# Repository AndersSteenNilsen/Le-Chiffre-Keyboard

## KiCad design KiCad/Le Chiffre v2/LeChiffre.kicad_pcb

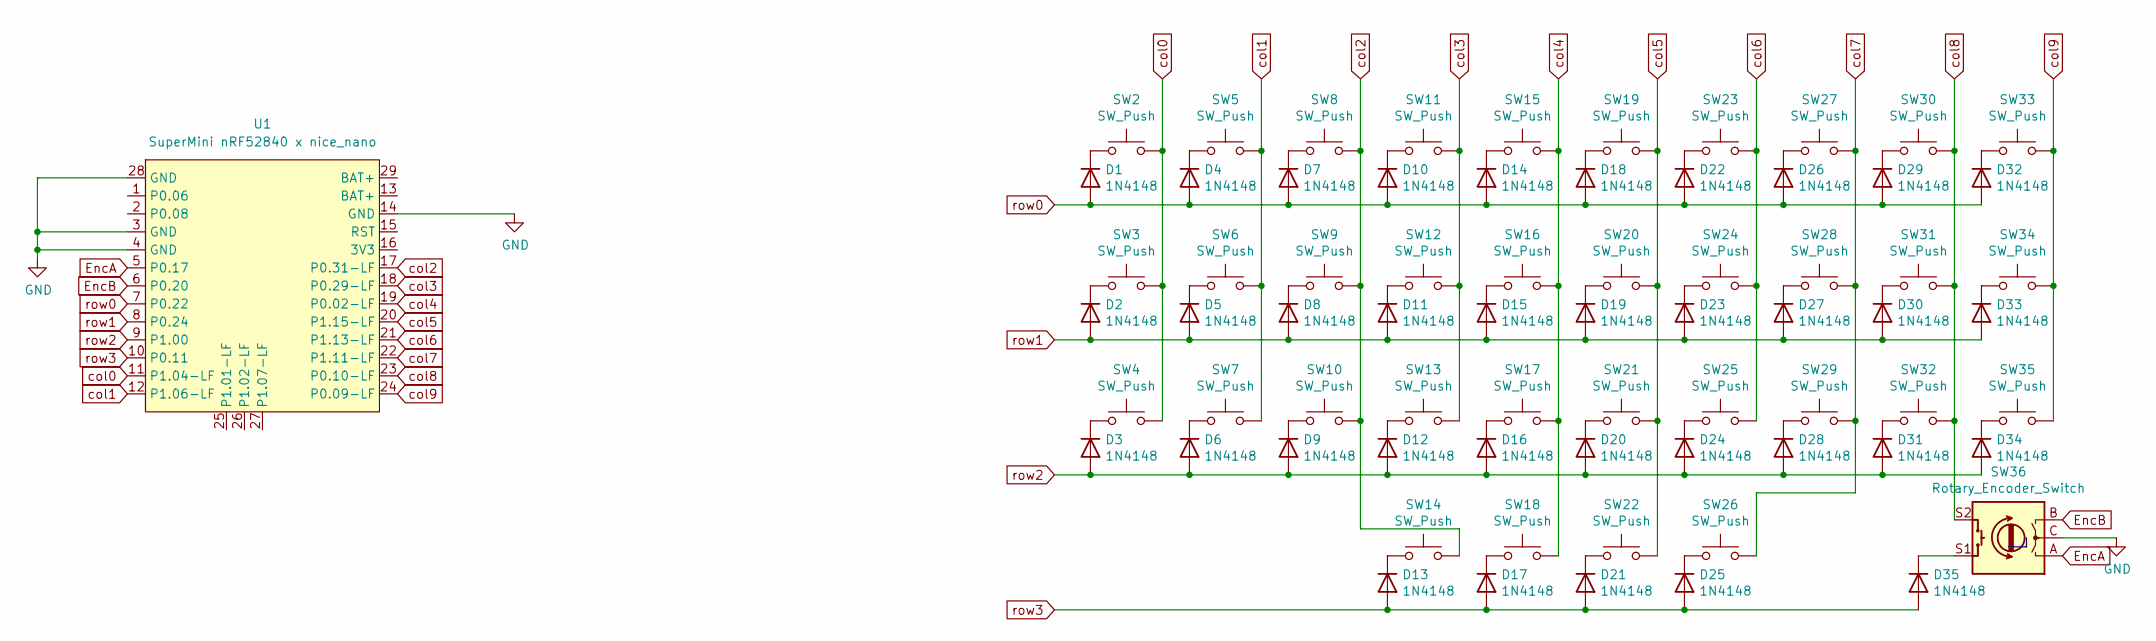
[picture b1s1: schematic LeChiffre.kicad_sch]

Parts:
D1, D2, D3, D4, D5, D6, D7, D8, D9, D10, D11, D12, D13, D14, D15, D16, D17, D18, D19, D20, D21, D22, D23, D24, D25, D26, D27, D28, D29, D30, D31, D32, D33, D34, D35: 1N4148; D_SOD123
SW2, SW3, SW4, SW5, SW6, SW7, SW8, SW9, SW10, SW11, SW12, SW13, SW14, SW15, SW16, SW17, SW19, SW20, SW21, SW23, SW24, SW25, SW26, SW27, SW28, SW29, SW30, SW31, SW32, SW33, SW34, SW35: SW_Push; MX-Alps-Choc-1U-NoLED
SW18, SW22: SW_Push; MX-Alps-Choc-2U-StabFlip
SW36: Rotary_Encoder_Switch; RotaryEncoder_Alps_EC12E-Switch_Vertical_H20mm_CircularMoun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
U1: SuperMini nRF52840 x nice_nano; supermini_x_nice_nano

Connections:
EncA: SW36.A, U1.5 (P0.17)
EncB: SW36.B, U1.6 (P0.20)
GND: SW36.C, U1.3 (GND), U1.4 (GND), U1.14 (GND), U1.28 (GND)
unnamed: D1.1 (K), SW2.1
unnamed: D2.1 (K), SW3.1
unnamed: D3.1 (K), SW4.1
unnamed: D4.1 (K), SW5.1
unnamed: D5.1 (K), SW6.1
unnamed: D6.1 (K), SW7.1
unnamed: D7.1 (K), SW8.1
unnamed: D8.1 (K), SW9.1
unnamed: D9.1 (K), SW10.1
unnamed: D10.1 (K), SW11.1
unnamed: D11.1 (K), SW12.1
unnamed: D12.1 (K), SW13.1
unnamed: D13.1 (K), SW14.1
unnamed: D14.1 (K), SW15.1
unnamed: D15.1 (K), SW16.1
unnamed: D16.1 (K), SW17.1
unnamed: D17.1 (K), SW18.1
unnamed: D18.1 (K), SW19.1
unnamed: D19.1 (K), SW20.1
unnamed: D20.1 (K), SW21.1
unnamed: D21.1 (K), SW22.1
unnamed: D22.1 (K), SW23.1
unnamed: D23.1 (K), SW24.1
unnamed: D24.1 (K), SW25.1
unnamed: D25.1 (K), SW26.1
unnamed: D26.1 (K), SW27.1
unnamed: D27.1 (K), SW28.1
unnamed: D28.1 (K), SW29.1
unnamed: D29.1 (K), SW30.1
unnamed: D30.1 (K), SW31.1
unnamed: D31.1 (K), SW32.1
unnamed: D32.1 (K), SW33.1
unnamed: D33.1 (K), SW34.1
unnamed: D34.1 (K), SW35.1
unnamed: D35.1 (K), SW36.S1
col0: SW2.2, SW3.2, SW4.2, U1.11 (P1.04-LF)
col1: SW5.2, SW6.2, SW7.2, U1.12 (P1.06-LF)
col2: SW8.2, SW9.2, SW10.2, SW14.2, U1.17 (P0.31-LF)
col3: SW11.2, SW12.2, SW13.2, U1.18 (P0.29-LF)
col4: SW15.2, SW16.2, SW17.2, SW18.2, U1.19 (P0.02-LF)
col5: SW19.2, SW20.2, SW21.2, SW22.2, U1.20 (P1.15-LF)
col6: SW23.2, SW24.2, SW25.2, U1.21 (P1.13-LF)
col7: SW26.2, SW27.2, SW28.2, SW29.2, U1.22 (P1.11-LF)
col8: SW30.2, SW31.2, SW32.2, SW36.S2, U1.23 (P0.10-LF)
col9: SW33.2, SW34.2, SW35.2, U1.24 (P0.09-LF)
row0: D1.2 (A), D4.2 (A), D7.2 (A), D10.2 (A), D14.2 (A), D18.2 (A), D22.2 (A), D26.2 (A), D29.2 (A), D32.2 (A), U1.7 (P0.22)
row1: D2.2 (A), D5.2 (A), D8.2 (A), D11.2 (A), D15.2 (A), D19.2 (A), D23.2 (A), D27.2 (A), D30.2 (A), D33.2 (A), U1.8 (P0.24)
row2: D3.2 (A), D6.2 (A), D9.2 (A), D12.2 (A), D16.2 (A), D20.2 (A), D24.2 (A), D28.2 (A), D31.2 (A), D34.2 (A), U1.9 (P1.00)
row3: D13.2 (A), D17.2 (A), D21.2 (A), D25.2 (A), D35.2 (A), U1.10 (P0.11)

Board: 2 copper layers, 71 parts (35 on the bottom side), 52 nets, no tracks yet.

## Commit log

2025-06-11 First commit, removing vias and tracks and mcu, adding nice_nano/supermioni/promicro
